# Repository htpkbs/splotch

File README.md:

# NB!

The layout of this doesn't work! The row/column hookups to the I/O expander aren't split between the `A` and `B` GPIO ports, so they don't work with the typical custom `matrix.c` that's used for other keyboards that use an I/O expander.

This particular PCB has been effectively abandoned ([see the nikon PCB for a somewhat similar split ergonomic board](https://github.com/htpkbs/nikon)) so this repository will be archived.

# Overview

A split keyboard with a layout inspired by the [Iris](https://keeb.io/products/iris-keyboard-split-ergonomic-keyboard) and through-hole components inspired by the [plaid](https://github.com/hsgw/plaid). It may or may not be easier to find keycap sets that fit this layout with the correct legends (most base GMK sets should work, with the addition of space keys). It also has a rotary encoder on the right half.

# Key Layout

The key layout looks like this (rotary encoder not included). (Thanks to [Keyboard Layout Editor](http://www.keyboard-layout-editor.com/) for the image.)

This is the corresponding data for pasting into Keyboard Layout Editor:

```
[{x:0.75,c:"#b80000",t:"#f5f5f5",a:5,f:5},"~\n`","!\n1","@\n2","#\n3","$\n4","%\n5",{x:4},"^\n6","&\n7","*\n8","(\n9",")\n0","_\n-","+\n="],
[{x:0.25,a:7,f:2,w:1.5},"TAB",{c:"#f5f5f5",t:"#424242",f:5},"Q","W","E","R","T",{x:4},"Y","U","I","O","P",{a:5},"{\n[","}\n]"],
[{c:"#b80000",t:"#f5f5f5",a:7,f:2,w:1.75},"CONTROL",{c:"#f5f5f5",t:"#424242",f:5},"A","S","D","F","G",{x:4},"H","J","K","L",{a:5},":\n;","\"\n'",{c:"#b80000",t:"#f5f5f5",a:7,f:2},"ENTER"],
[{w:1.75},"SHIFT",{c:"#f5f5f5",t:"#424242",f:5},"Z","X","C","V","B",{x:4},"N","M",{a:5},"<\n,",">\n.","?\n/",{c:"#b80000",t:"#f5f5f5",a:7,f:2,w:1.25},"SHIFT"],
[{y:0.25,x:3},"ALT",{w:1.25},"CODE","LOWER",{x:5},"RAISE",{w:1.25},"CODE","FN"],
[{r:30,rx:6.75,ry:3,y:0.5,x:0.75,f:5},""],
[{x:0.75,f:2},""],
[{r:-30,rx:10.75,y:0.5,x:-1.75,f:5},""],
[{x:-1.75,f:2},""]
```

# PCB Renders

## Left

## Right

# Case/Back Plates

There are no plate or full case files (sandwich style is hard with exposed components...) but there are some DXF files to print back plates for each half. You can mount the PCBs to these back plates using M2 size screws and standoffs. [Here is the file for the left back plate](assets/case-left.dxf) and [here is the file for the right back plate](assets/case-right.dxf).

# Schematic

There is a PDF of the [schematic of the left half here](assets/schematic-left.pdf) and the [schematic of the right half here](assets/schematic-right.pdf). There is a [bill of materials (BOM) here](BOM.md).

# AVR Notes

There will be some notes about programming the microcontroller with [USBaspLoader](https://github.com/baerwolf/USBaspLoader) here. [The ATmega328P datasheet is here](https://ww1.microchip.com/downloads/en/DeviceDoc/Atmel-7810-Automotive-Microcontrollers-ATmega328P_Datasheet.pdf) and [the MC32017 datasheet is here](https://ww1.microchip.com/downloads/en/devicedoc/20001952c.pdf). The keyboard does not use QMK's split keyboard functionality, but extends the number of available I/O pins by communicating with I2C over the TRRS cable. This means it should appear as a single, non-split keyboard to QMK, and has the benefit of requiring fewer components on the right half of the keyboard.

# Sublicenses

* Thank you to [coseyfannitutti](https://github.com/coseyfannitutti) for the footprints `D_DO-35_SOD27_P5.08mm_Horizontal.kicad_mod` and `USB_C_GCT_USB4085.kicad_mod`. [The Creative Commons license for these is included here](LICENSE.CFTKB).
* Thanks to [ai03-2725](https://github.com/ai03-2725) for the `MX*` symbols. [The MIT license for these is included here](LICENSE.ai03).

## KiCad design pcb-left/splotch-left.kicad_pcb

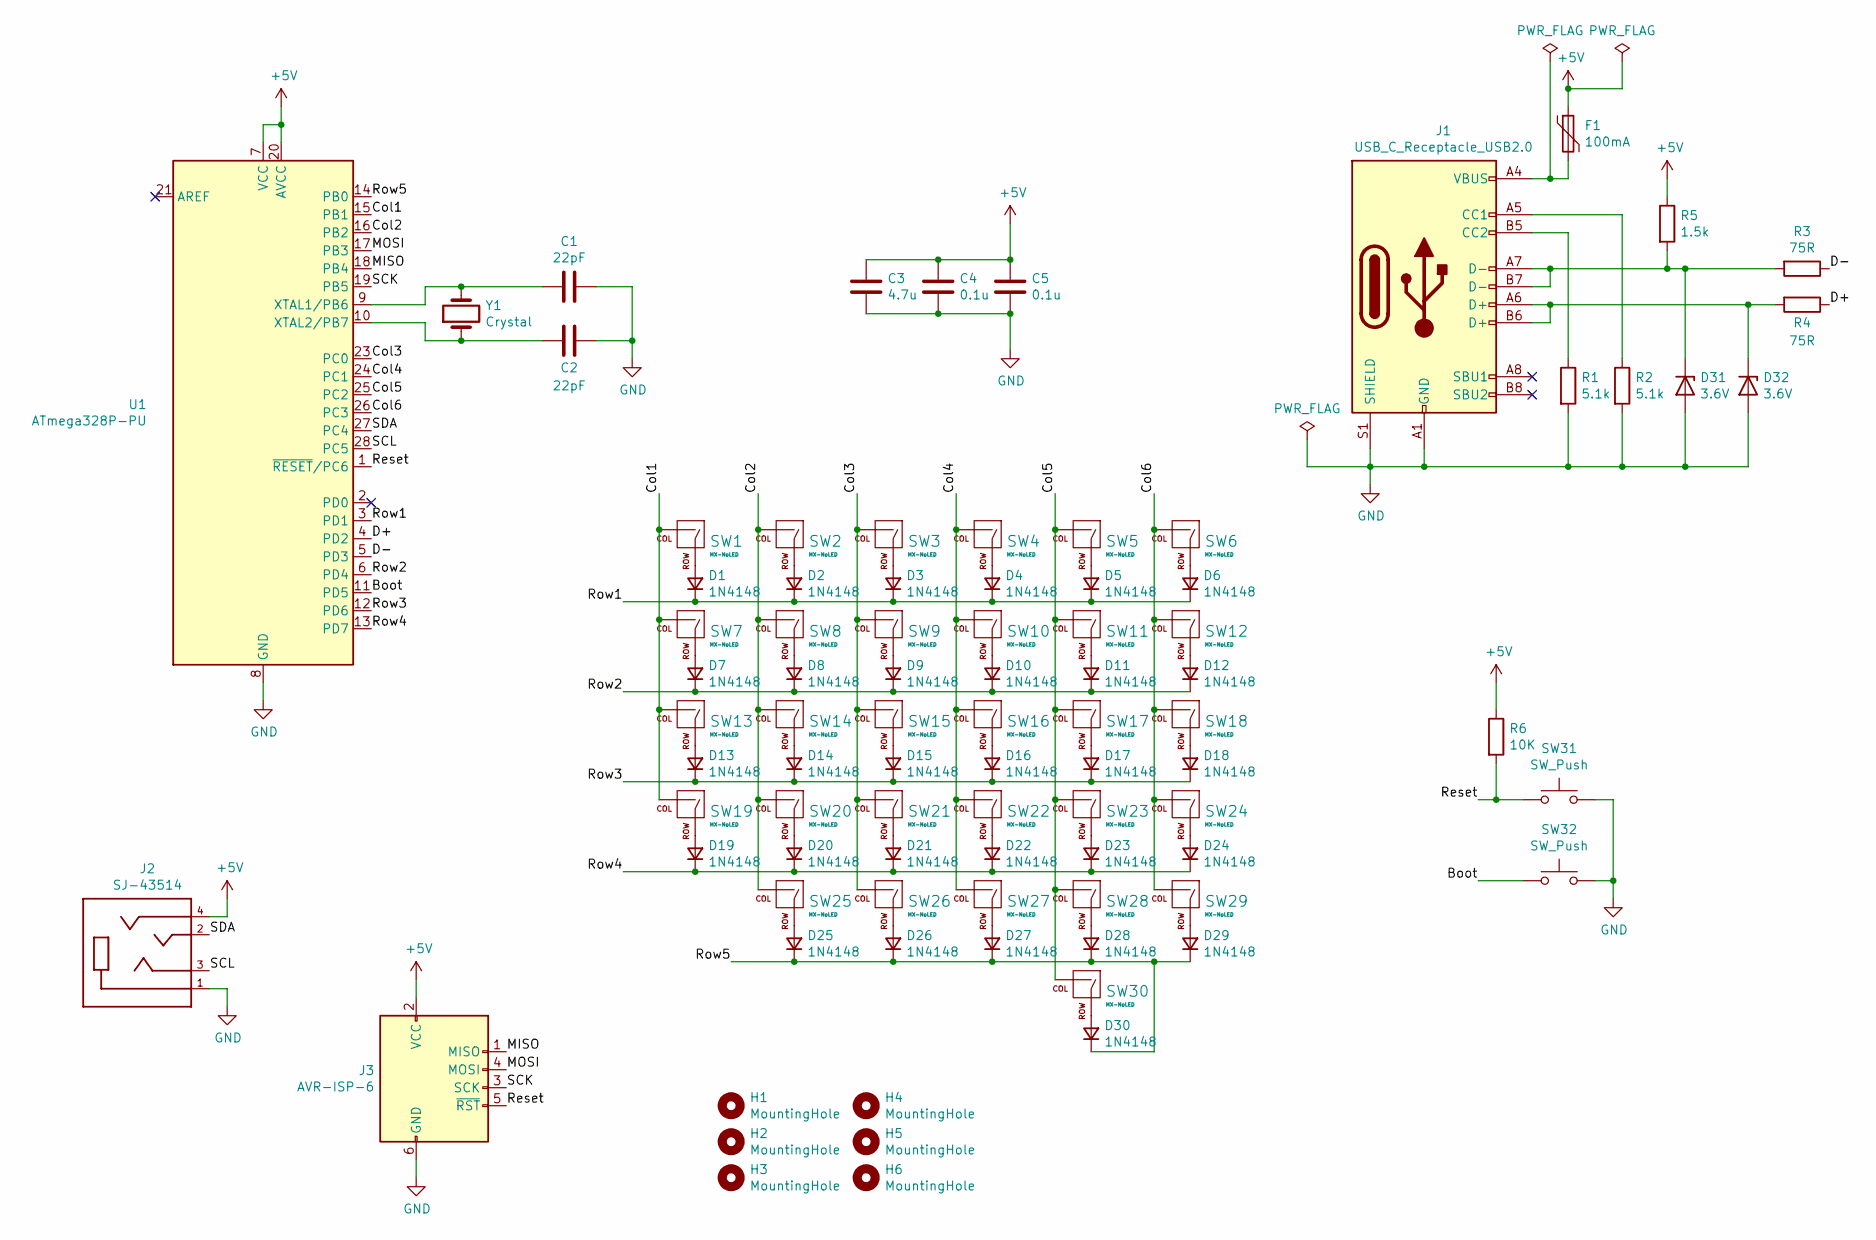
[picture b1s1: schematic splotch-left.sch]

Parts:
C1, C2: 22pF; C_Rect_L4.0mm_W2.5mm_P2.50mm
C3: 4.7u; C_Radial_D4.0mm_H7.0mm_P1.50mm
C4, C5: 0.1u; C_Rect_L4.0mm_W2.5mm_P2.50mm
D1, D2, D3, D4, D5, D6, D7, D8, D9, D10, D11, D12, D13, D14, D15, D16, D17, D18, D19, D20, D21, D22, D23, D24, D25, D26, D27, D28, D29, D30: 1N4148; D_DO-35_SOD27_P5.08mm_Horizontal
D31, D32: 3.6V; D_DO-35_SOD27_P5.08mm_Horizontal
F1: 100mA; Fuse_Littelfuse_395Series
H1, H2, H3, H4, H5, H6: MountingHole; MountingHole_2.2mm_M2
J1: USB_C_Receptacle_USB2.0; USB_C_GCT_USB4085
J2: SJ-43514; CUI_SJ-43514
J3: AVR-ISP-6; PinHeader_2x03_P2.54mm_Vertical
R1, R2: 5.1k; R_Axial_DIN0204_L3.6mm_D1.6mm_P5.08mm_Horizontal
R3, R4: 75R; R_Axial_DIN0204_L3.6mm_D1.6mm_P5.08mm_Horizontal
R5: 1.5k; R_Axial_DIN0204_L3.6mm_D1.6mm_P5.08mm_Horizontal
R6: 10K; R_Axial_DIN0204_L3.6mm_D1.6mm_P5.08mm_Horizontal
SW1, SW2, SW3, SW4, SW5, SW6, SW8, SW9, SW10, SW11, SW12, SW14, SW15, SW16, SW17, SW18, SW20, SW21, SW22, SW23, SW24, SW25, SW27, SW28, SW29, SW30: MX-NoLED; MX-1U-NoLED
SW7: MX-NoLED; MX-1.5U-NoLED
SW13, SW19: MX-NoLED; MX-1.75U-NoLED
SW26: MX-NoLED; MX-1.25U-NoLED
SW31, SW32: SW_Push; SW_PUSH_6mm_H4.3mm
U1: ATmega328P-PU; DIP-28_W7.62mm
Y1: Crystal; Crystal_HC49-4H_Vertical

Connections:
+5V: C3.1, C4.1, C5.1, F1.1, J2.4, J3.2 (VCC), R5.1, R6.1, U1.7 (VCC), U1.20 (AVCC)
/Boot: SW32.1, U1.11 (PD5)
/Col1: SW1.2 (ROW), SW7.2 (ROW), SW13.2 (ROW), SW19.2 (ROW), U1.15 (PB1)
/Col2: SW2.2 (ROW), SW8.2 (ROW), SW14.2 (ROW), SW20.2 (ROW), SW25.2 (ROW), U1.16 (PB2)
/Col3: SW3.2 (ROW), SW9.2 (ROW), SW15.2 (ROW), SW21.2 (ROW), SW26.2 (ROW), U1.23 (PC0)
/Col4: SW4.2 (ROW), SW10.2 (ROW), SW16.2 (ROW), SW22.2 (ROW), SW27.2 (ROW), U1.24 (PC1)
/Col5: SW5.2 (ROW), SW11.2 (ROW), SW17.2 (ROW), SW23.2 (ROW), SW28.2 (ROW), SW30.2 (ROW), U1.25 (PC2)
/Col6: SW6.2 (ROW), SW12.2 (ROW), SW18.2 (ROW), SW24.2 (ROW), SW29.2 (ROW), U1.26 (PC3)
/D+: R4.1, U1.4 (PD2)
/D-: R3.1, U1.5 (PD3)
/MISO: J3.1 (MISO), U1.18 (PB4)
/MOSI: J3.4 (MOSI), U1.17 (PB3)
/Reset: J3.5 (~RST), R6.2, SW31.1, U1.1 (~RESET~/PC6)
/Row1: D1.1 (K), D2.1 (K), D3.1 (K), D4.1 (K), D5.1 (K), D6.1 (K), U1.3 (PD1)
/Row2: D7.1 (K), D8.1 (K), D9.1 (K), D10.1 (K), D11.1 (K), D12.1 (K), U1.6 (PD4)
/Row3: D13.1 (K), D14.1 (K), D15.1 (K), D16.1 (K), D17.1 (K), D18.1 (K), U1.12 (PD6)
/Row4: D19.1 (K), D20.1 (K), D21.1 (K), D22.1 (K), D23.1 (K), D24.1 (K), U1.13 (PD7)
/Row5: D25.1 (K), D26.1 (K), D27.1 (K), D28.1 (K), D29.1 (K), D30.1 (K), U1.14 (PB0)
/SCK: J3.3 (SCK), U1.19 (PB5)
/SCL: J2.3, U1.28 (PC5)
/SDA: J2.2, U1.27 (PC4)
GND: C1.1, C2.2, C3.2, C4.2, C5.2, D31.2 (A), D32.2 (A), J1.A1 (GND), J1.A12 (GND), J1.B1 (GND), J1.B12 (GND), J1.S1 (SHIELD), J2.1, J3.6 (GND), R1.2, R2.2, SW31.2, SW32.2, U1.8 (GND), U1.22 (GND)
unnamed: C1.2, U1.9 (XTAL1/PB6), Y1.2
unnamed: C2.1, U1.10 (XTAL2/PB7), Y1.1
unnamed: D1.2 (A), SW1.1 (COL)
unnamed: D2.2 (A), SW2.1 (COL)
unnamed: D3.2 (A), SW3.1 (COL)
unnamed: D4.2 (A), SW4.1 (COL)
unnamed: D5.2 (A), SW5.1 (COL)
unnamed: D6.2 (A), SW6.1 (COL)
unnamed: D7.2 (A), SW7.1 (COL)
unnamed: D8.2 (A), SW8.1 (COL)
unnamed: D9.2 (A), SW9.1 (COL)
unnamed: D10.2 (A), SW10.1 (COL)
unnamed: D11.2 (A), SW11.1 (COL)
unnamed: D12.2 (A), SW12.1 (COL)
unnamed: D13.2 (A), SW13.1 (COL)
unnamed: D14.2 (A), SW14.1 (COL)
unnamed: D15.2 (A), SW15.1 (COL)
unnamed: D16.2 (A), SW16.1 (COL)
unnamed: D17.2 (A), SW17.1 (COL)
unnamed: D18.2 (A), SW18.1 (COL)
unnamed: D19.2 (A), SW19.1 (COL)
unnamed: D20.2 (A), SW20.1 (COL)
unnamed: D21.2 (A), SW21.1 (COL)
unnamed: D22.2 (A), SW22.1 (COL)
unnamed: D23.2 (A), SW23.1 (COL)
unnamed: D24.2 (A), SW24.1 (COL)
unnamed: D25.2 (A), SW25.1 (COL)
unnamed: D26.2 (A), SW26.1 (COL)
unnamed: D27.2 (A), SW27.1 (COL)
unnamed: D28.2 (A), SW28.1 (COL)
unnamed: D29.2 (A), SW29.1 (COL)
unnamed: D30.2 (A), SW30.1 (COL)
unnamed: D31.1 (K), J1.A7 (D-), J1.B7 (D-), R3.2, R5.2
unnamed: D32.1 (K), J1.A6 (D+), J1.B6 (D+), R4.2
unnamed: F1.2, J1.A4 (VBUS), J1.A9 (VBUS), J1.B4 (VBUS), J1.B9 (VBUS)
unnamed: J1.A5 (CC1), R2.1
unnamed: J1.B5 (CC2), R1.1

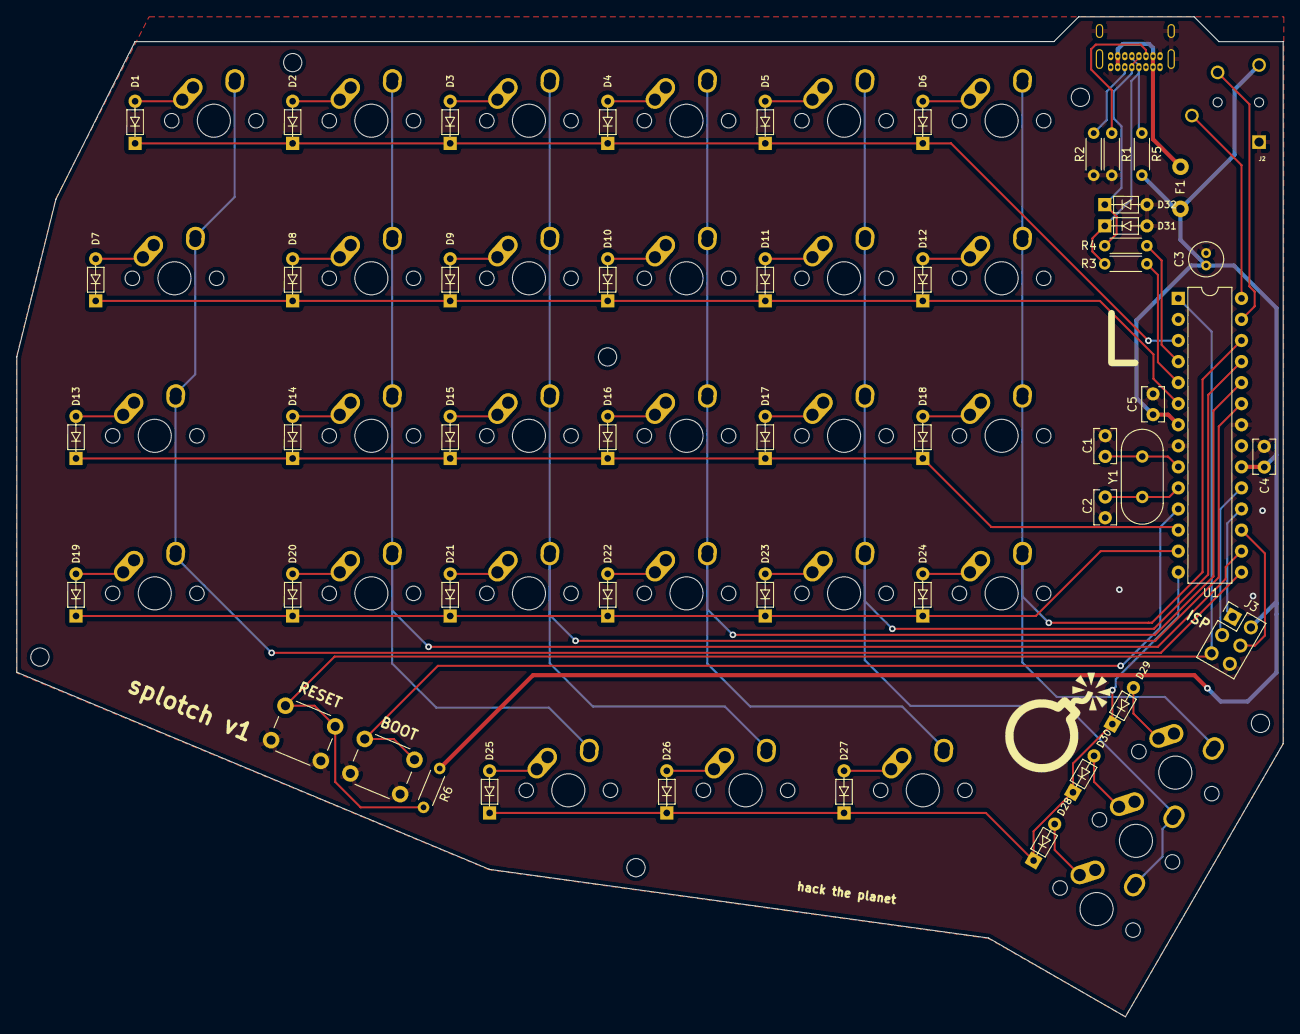
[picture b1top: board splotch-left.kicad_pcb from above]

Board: 2 copper layers, 152.7 x 120.6 mm, 87 parts (1 on the bottom side), 59 nets.

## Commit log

2021-03-18 initial
2021-03-18 Add back plate/case files
2021-03-18 updated pcb renders
2021-03-18 typo
2021-03-18 add BOM
2021-03-19 plural?
2021-03-22 more accurate layout
2022-03-12 archive with note

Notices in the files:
pcb-left/splotch-left.kicad_pcb:
License: BSD 2-Clause
